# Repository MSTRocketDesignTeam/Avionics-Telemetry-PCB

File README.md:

View this project on [CADLAB.io](https://cadlab.io/project/24983). 

# Overview

This repository contains the PCB files for the main Rocket Telemetry project.

## Purpose and Motivation
This project aims to create flight-rated PCBs that can collect information about the team's rockets as they are launched.

The primary impetus for this project is to develop a student-designed solution to keep the team from losing rockets. This means that these boards must contain and interface with the electronics required to track and analyze a rocket mid-flight and indicate the rocket landing site location to the team back at the launch site to aid in recovery efforts.

The second purpose of this board is to collect and stream performance data about the rocket during all stages of its flight. This data will come from onboard sensors that measure the rocket’s acceleration, altitude, speed, orientation, etc. This will initially only be stored onboard the rocket, with the long-term goal of feeding a real-time 3D model simulation of the rocket’s flight to the team at the launch site. It should also be a goal to include future capabilities for interfacing with external sensors, such as thermocouples, pressure transducers, cameras, and more.

## Inspirations

Initial developments of this board are to be a direct replacement for a Telemetrum V3, with features and design optimizations to be implemented in future revisions.

A [Telemetrum V3](https://altusmetrum.org/TeleMetrum/) is an amateur rocketry telemetry solution from [Altus Metrum](https://altusmetrum.org/index.html).

[Signal](https://bps.space/signal/) from [BPS.Space](https://bps.space/) is a flight computer first and a data collection solution second. It is designed to stream data to the ground station, although it is likely insufficient for the large 10-30k ft class rockets that our team constructs.

An excellent KiCAD tutorial around making a small thumb-drive-sized PCB with an STM32, RF, and USB components: [here on YouTube by Phil's Lab](https://www.youtube.com/watch?v=14_jh3nLSsU) and is an excellent tutorial on using circuit design software and the process/approach you go through making something like this. Highly recommended to watch and maybe take some notes on. This is a solid start for our telemetry board.

# Features

#### Physical

* Expected Size: 53 x 69 mm (Arduino Uno)
* Best Size: Around 75 x 25 mm if possible
* Thin/Long is better than Square
* Rectangular shape w/ rounded edges
* Screw Mounting Holes

#### Primary Components

* STM32 Family Microcontroller
* 900MHz Radio Module
* GPS Receiver
* External RF Antenna Connector

#### Sensors

* Accelerometer
* Magnetometer
* Barometer
* Gyroscope
* Temperature

#### Data

* Flash Storage Chip for inflight capture
* Micro SD Card Reader for postflight storage
* Debugging/programming header

#### Power

* Connection to LiPo Packs
* Coin Cell/Capacitor Battery Backup
* No charge controller
* Low-power mode preflight

# Companion Documentation

[Telemetry Board R&D Documentation Folder - Google Drive](https://drive.google.com/drive/folders/1-Ft9_IYGoKeQ8SOpWUMPCNhws5y90gv3?usp=sharing)

[Component Comparison - Google Sheet](https://docs.google.com/spreadsheets/d/1QPZUW1DP2L5ciMKxbgeHV3uC0-h4SxSqm0nYhaIsA54/edit?usp=sharing)

[Telemetrum V3 Features and Components - Google Doc](https://docs.google.com/document/d/1UKlisEx7MZwDFethEzJ8d39NXyabVl6lI_5ZflczvP4/edit?usp=sharing)

[Telemetry Board Requirement Brainstorm - Google Doc](https://docs.google.com/document/d/1sqFQGxX3MVceV2B7MoNJb_ZmXdHjXhyEQbpknLjsYw0/edit?usp=sharing)

[Telemetry Notepad - Google Doc](https://docs.google.com/document/d/1K5M_XsDRmasx09W511Fg23m5dxfRa6N_FNR6dFqZZKQ/edit?usp=sharing)

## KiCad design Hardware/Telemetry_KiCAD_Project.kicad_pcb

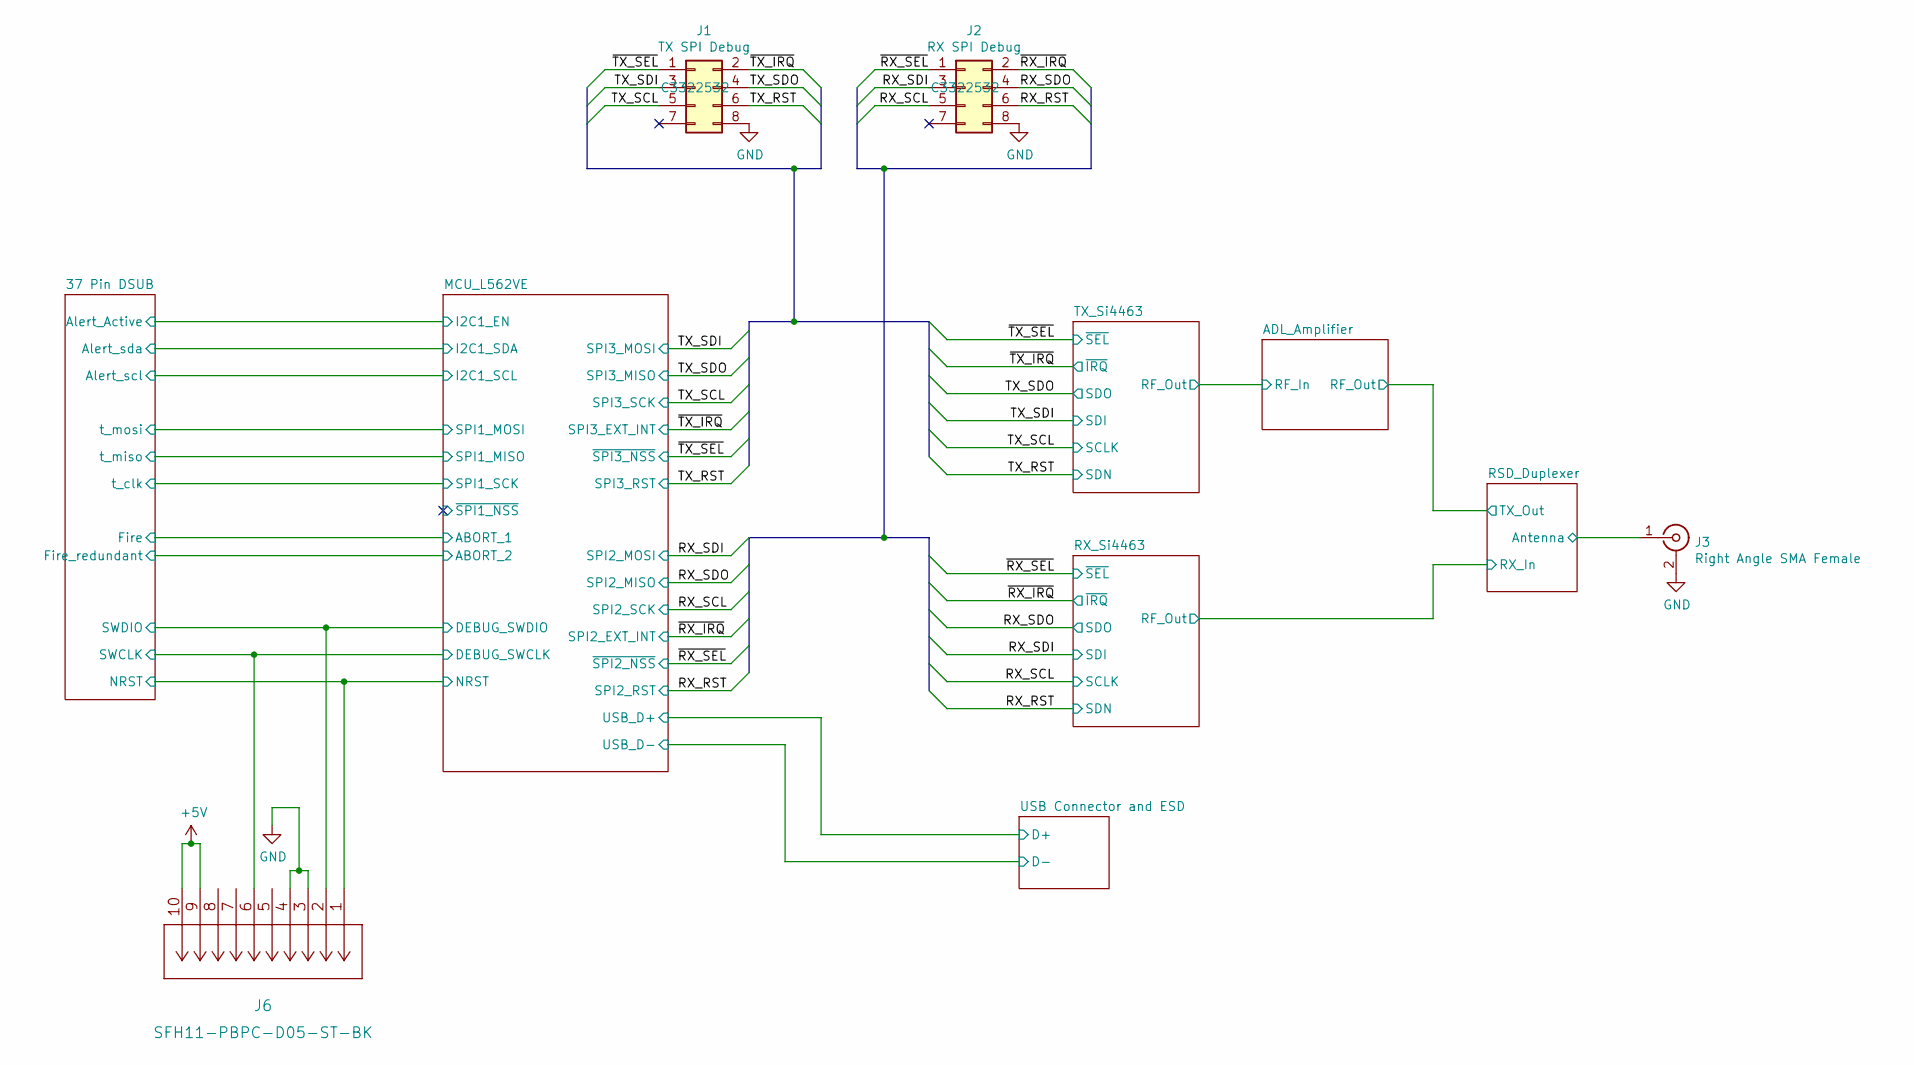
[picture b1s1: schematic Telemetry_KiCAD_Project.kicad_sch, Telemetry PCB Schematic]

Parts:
J1: TX SPI Debug; PinHeader_2x04_P2.54mm_Vertical; LCSC C3322532
J2: RX SPI Debug; PinHeader_2x04_P2.54mm_Vertical; LCSC C3322532
J3: Right Angle SMA Female; SMA_Molex_73251-2200_Horizontal; LCSC C3174425
J6: SFH11-PBPC-D05-ST-BK

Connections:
+5V: J6.9, J6.10; also elsewhere on the board
/37 Pin DSUB/SWCLK: J6.6; also elsewhere on the board
/37 Pin DSUB/SWDIO: J6.2; also elsewhere on the board
/MCU_L562VE/~RESET: J6.1; also elsewhere on the board
/RSD_Duplexer/Antenna: J3.1 (In); also elsewhere on the board
/RX_RST: J2.6; also elsewhere on the board
/RX_SCL: J2.5; also elsewhere on the board
/RX_SDI: J2.3; also elsewhere on the board
/RX_SDO: J2.4; also elsewhere on the board
/TX_RST: J1.6; also elsewhere on the board
/TX_SCL: J1.5; also elsewhere on the board
/TX_SDI: J1.3; also elsewhere on the board
/TX_SDO: J1.4; also elsewhere on the board
/~RX_IRQ: J2.2; also elsewhere on the board
/~RX_SEL: J2.1; also elsewhere on the board
/~TX_IRQ: J1.2; also elsewhere on the board
/~TX_SEL: J1.1; also elsewhere on the board
GND: J1.8, J2.8, J3.2 (Ext), J6.3, J6.4; also elsewhere on the board

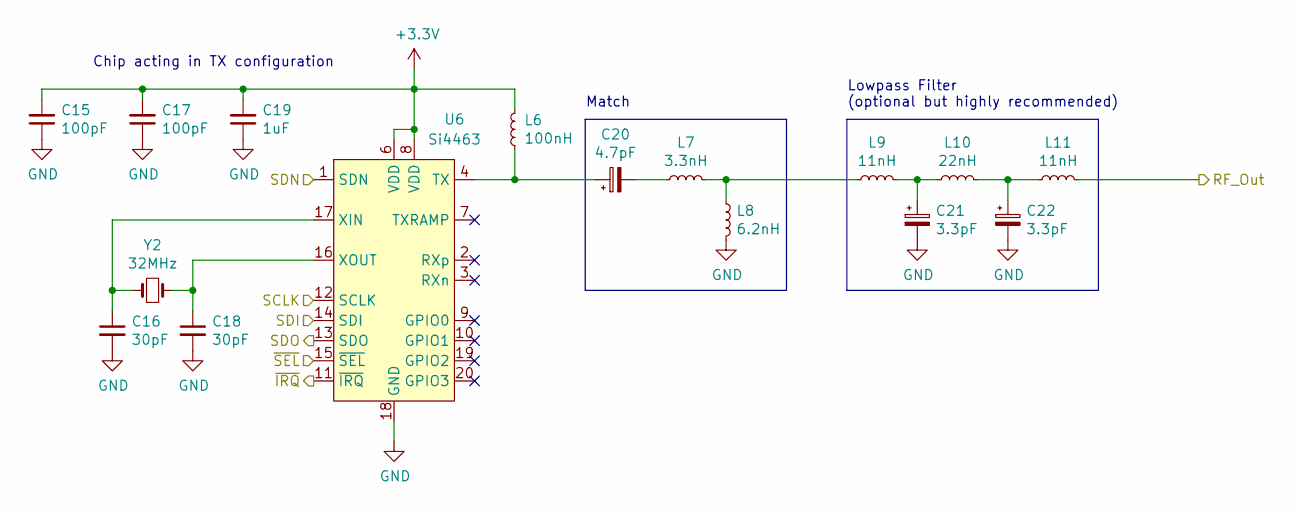
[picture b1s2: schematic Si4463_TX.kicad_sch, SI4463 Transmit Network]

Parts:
C15, C17: 100pF; C_0402_1005Metric; LCSC C1546
C16, C18: 30pF; C_0603_1608Metric_Pad1.08x0.95mm_HandSolder; LCSC C123555
C19: 1uF; C_0402_1005Metric; LCSC C52923
C20: 4.7pF; C_0402_1005Metric; LCSC C1569
C21, C22: 3.3pF; C_0402_1005Metric; LCSC C1565
L6: 100nH; L_0402_1005Metric; LCSC C22726
L7: 3.3nH; L_0402_1005Metric; LCSC C86064
L8: 6.2nH; L_0402_1005Metric; LCSC C87534
L9, L11: 11nH; L_0402_1005Metric; LCSC C27147
L10: 22nH; L_0402_1005Metric; LCSC C15178
U6: Si4463; QFN-20-1EP_4x4mm_P0.5mm_EP2.6x2.6mm_ThermalVias; LCSC C476202
Y2: 32MHz; XTAL_ABM7-32.000MHZ-D2Y-T; LCSC C1986810

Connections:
+3V3: C15.2, C17.2, C19.2, L6.2, U6.6 (VDD), U6.8 (VDD); also elsewhere on the board
/ADL_Amplifier/RF_In: L11.2; also elsewhere on the board
/TX_RST: U6.1 (SDN); also elsewhere on the board
/TX_SCL: U6.12 (SCLK); also elsewhere on the board
/TX_SDI: U6.14 (SDI); also elsewhere on the board
/TX_SDO: U6.13 (SDO); also elsewhere on the board
/~TX_IRQ: U6.11 (~IRQ); also elsewhere on the board
/~TX_SEL: U6.15 (~SEL); also elsewhere on the board
GND: C15.1, C16.2, C17.1, C18.2, C19.1, C21.2, C22.2, L8.2, U6.18 (GND), U6.21 (GND); also elsewhere on the board
unnamed: C16.1, U6.17 (XIN), Y2.1
unnamed: C18.1, U6.16 (XOUT), Y2.2
unnamed: C20.1, L6.1, U6.4 (TX)
unnamed: C20.2, L7.1
unnamed: C21.1, L9.2, L10.1
unnamed: C22.1, L10.2, L11.1
unnamed: L7.2, L8.1, L9.1

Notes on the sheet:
Match
Chip acting in TX configuration
Lowpass Filter (optional but highly recommended)

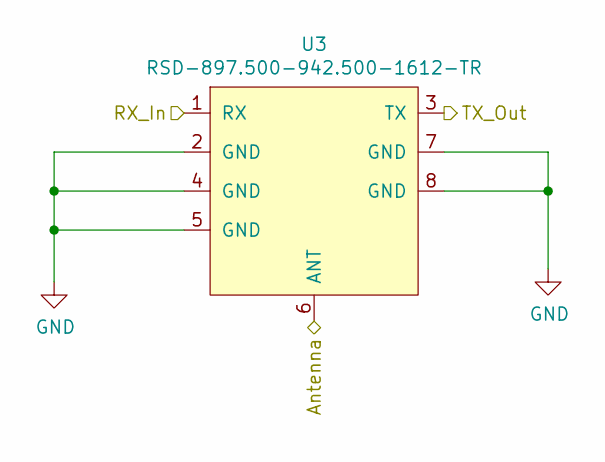
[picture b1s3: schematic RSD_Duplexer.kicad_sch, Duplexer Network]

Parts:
U3: RSD-897.500-942.500-1612-TR; LCSC C3271762

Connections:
/ADL_Amplifier/RF_Out: U3.3 (TX); also elsewhere on the board
/RSD_Duplexer/Antenna: U3.6 (ANT); also elsewhere on the board
/RSD_Duplexer/RX_In: U3.1 (RX); also elsewhere on the board
GND: U3.2 (GND), U3.4 (GND), U3.5 (GND), U3.7 (GND), U3.8 (GND); also elsewhere on the board

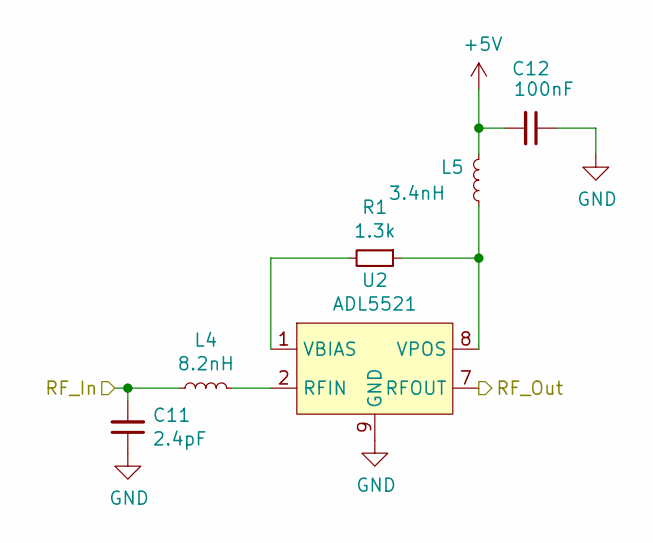
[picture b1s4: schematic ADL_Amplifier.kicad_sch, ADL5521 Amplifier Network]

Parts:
C11: 2.4pF; C_0402_1005Metric; LCSC C123475
C12: 100nF; C_0402_1005Metric; LCSC C307331
L4: 8.2nH; L_0402_1005Metric; LCSC C16208
L5: 3.4nH; L_0402_1005Metric; LCSC C86064
R1: 1.3k; R_0402_1005Metric; LCSC C25866
U2: ADL5521; LFCSP-8-1EP_3x3mm_P0.5mm_EP1.45x1.74mm; LCSC C657768

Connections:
+5V: C12.2, L5.2; also elsewhere on the board
/ADL_Amplifier/RF_In: C11.2, L4.1; also elsewhere on the board
/ADL_Amplifier/RF_Out: U2.7 (RFOUT); also elsewhere on the board
GND: C11.1, C12.1, U2.9 (GND); also elsewhere on the board
unnamed: L4.2, U2.2 (RFIN)
unnamed: L5.1, R1.1, U2.8 (VPOS)
unnamed: R1.2, U2.1 (VBIAS)

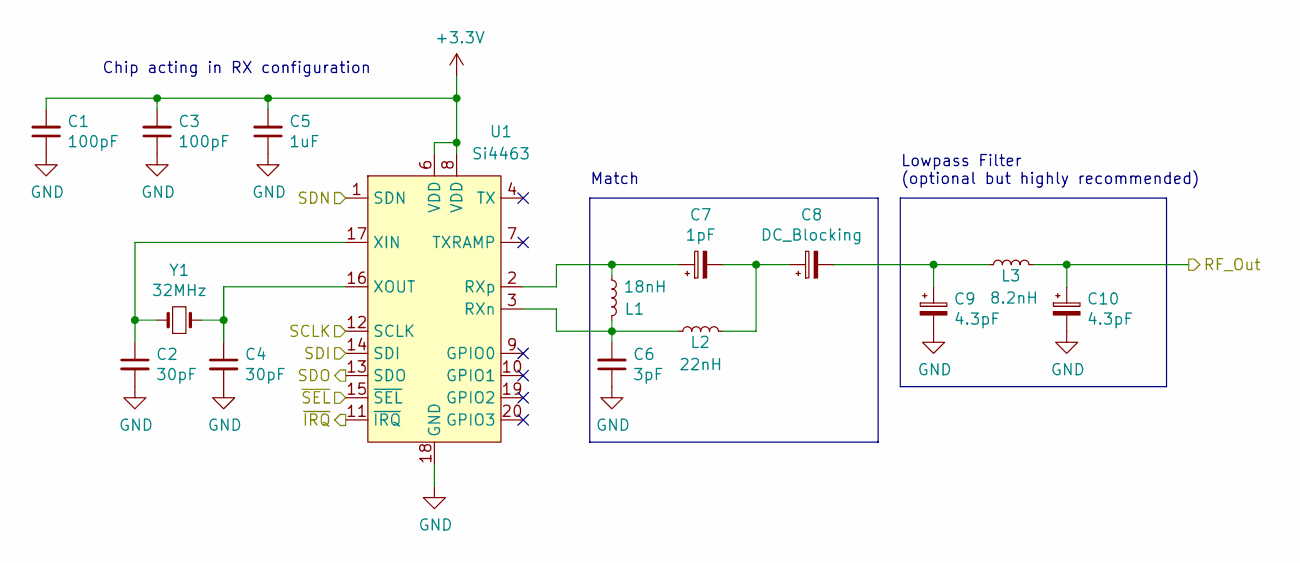
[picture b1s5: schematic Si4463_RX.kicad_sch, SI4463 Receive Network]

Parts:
C1, C3: 100pF; C_0402_1005Metric; LCSC C1546
C2, C4: 30pF; C_0603_1608Metric_Pad1.08x0.95mm_HandSolder; LCSC C123555
C5: 1uF; C_0402_1005Metric; LCSC C52923
C6: 3pF; C_0402_1005Metric; LCSC C115630
C7: 1pF; C_0402_1005Metric; LCSC C1550
C8: DC_Blocking; C_0402_1005Metric; LCSC C1550
C9, C10: 4.3pF; C_0402_1005Metric; LCSC C159803
L1: 18nH; L_0402_1005Metric; LCSC C24562
L2: 22nH; L_0402_1005Metric; LCSC C15178
L3: 8.2nH; L_0402_1005Metric; LCSC C16208
U1: Si4463; QFN-20-1EP_4x4mm_P0.5mm_EP2.6x2.6mm_ThermalVias; LCSC C476202
Y1: 32MHz; XTAL_ABM7-32.000MHZ-D2Y-T; LCSC C1986810

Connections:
+3V3: C1.2, C3.2, C5.2, U1.6 (VDD), U1.8 (VDD); also elsewhere on the board
/RSD_Duplexer/RX_In: C10.1, L3.2; also elsewhere on the board
/RX_RST: U1.1 (SDN); also elsewhere on the board
/RX_SCL: U1.12 (SCLK); also elsewhere on the board
/RX_SDI: U1.14 (SDI); also elsewhere on the board
/RX_SDO: U1.13 (SDO); also elsewhere on the board
/~RX_IRQ: U1.11 (~IRQ); also elsewhere on the board
/~RX_SEL: U1.15 (~SEL); also elsewhere on the board
GND: C1.1, C2.2, C3.1, C4.2, C5.1, C6.1, C9.2, C10.2, U1.18 (GND), U1.21 (GND); also elsewhere on the board
unnamed: C2.1, U1.17 (XIN), Y1.1
unnamed: C4.1, U1.16 (XOUT), Y1.2
unnamed: C6.2, L1.2, L2.1, U1.3 (RXn)
unnamed: C7.1, L1.1, U1.2 (RXp)
unnamed: C7.2, C8.1, L2.2
unnamed: C8.2, C9.1, L3.1

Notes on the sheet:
Chip acting in RX configuration
Lowpass Filter (optional but highly recommended)
Match

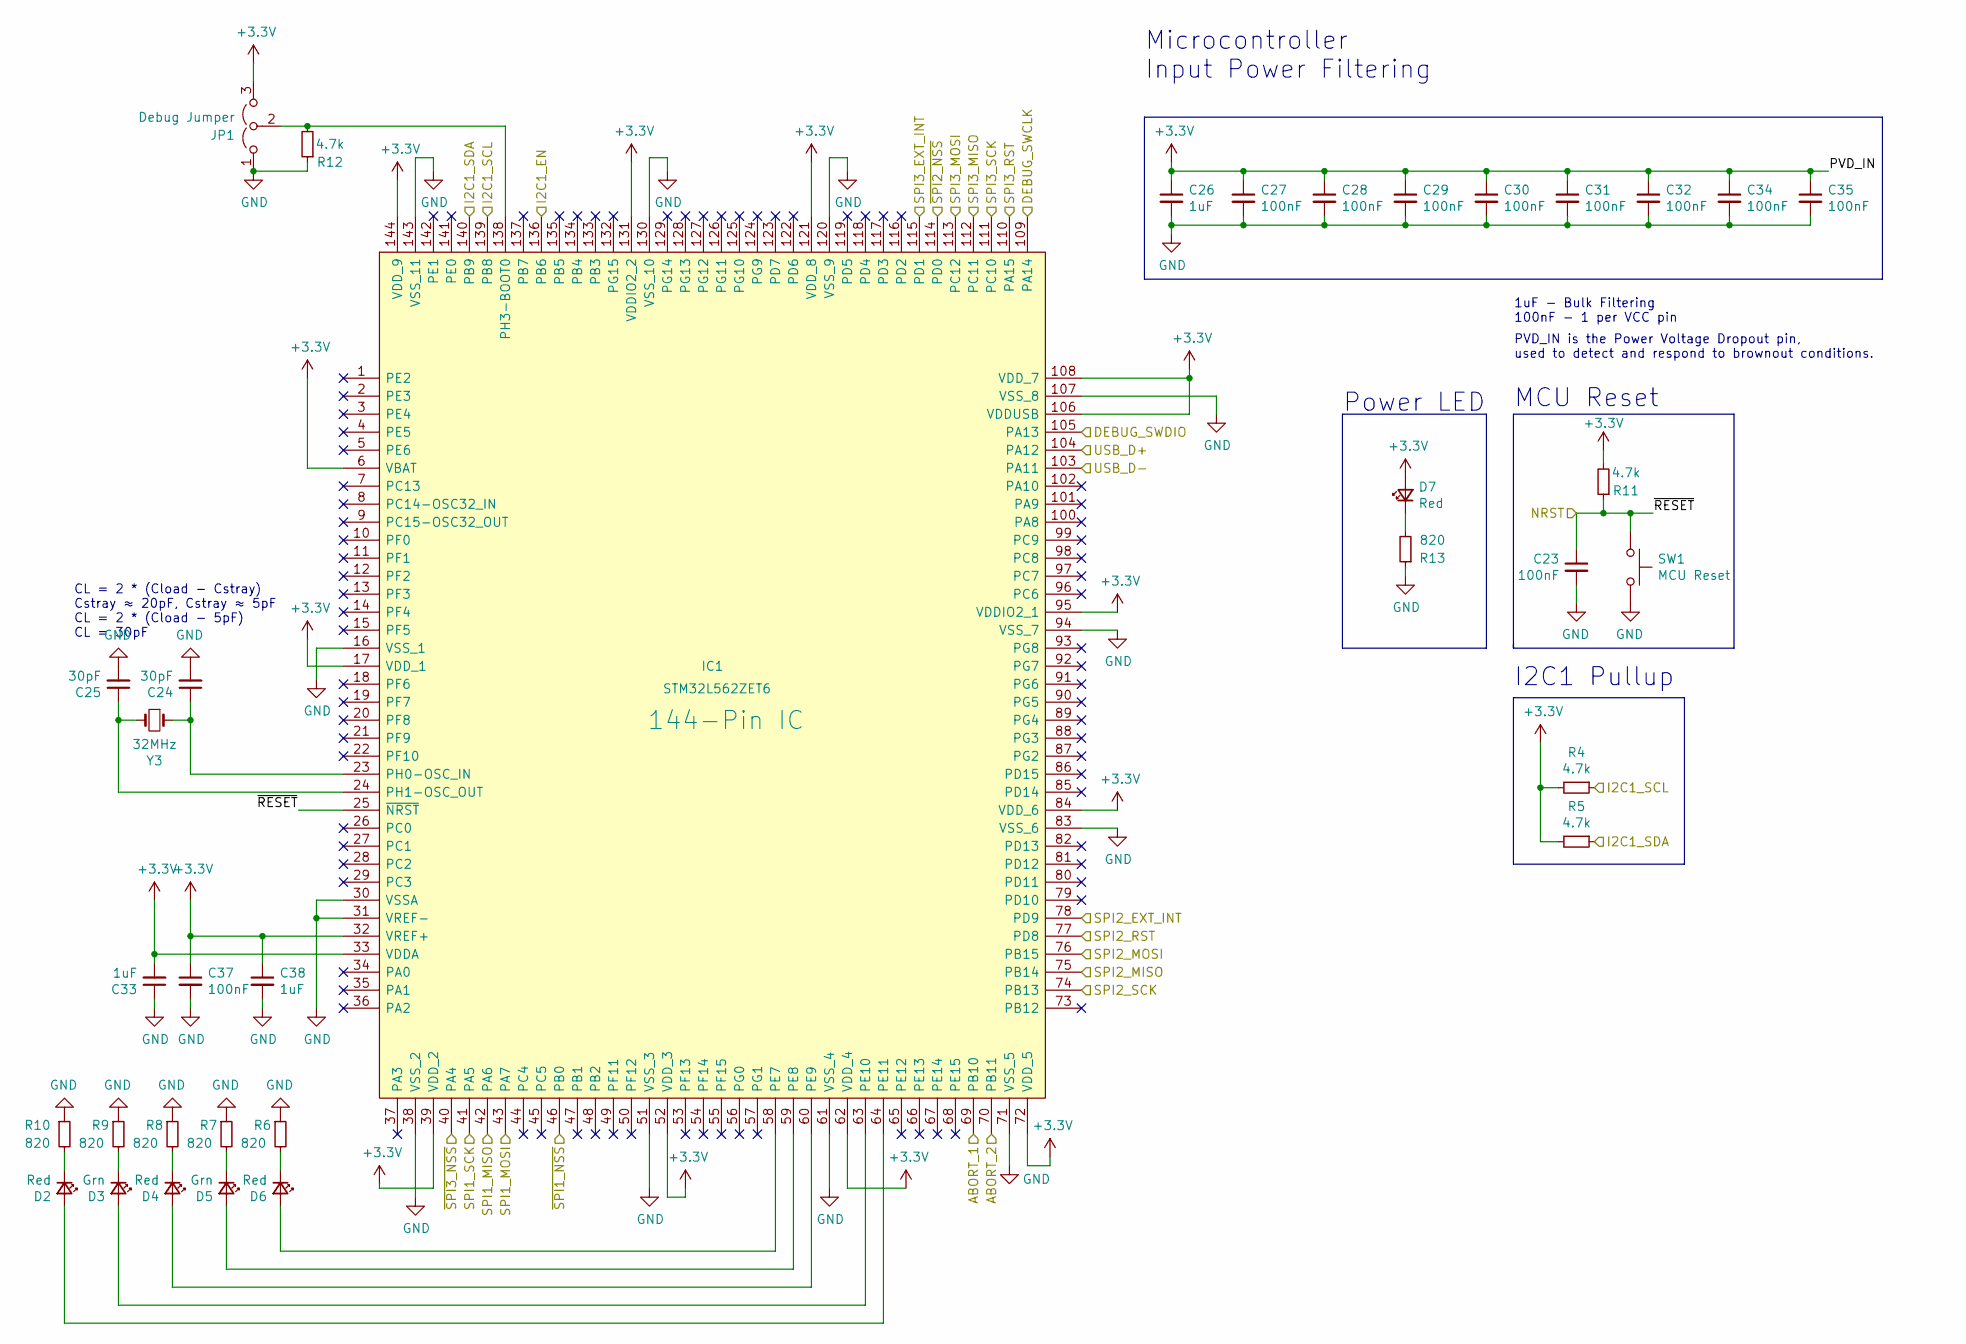
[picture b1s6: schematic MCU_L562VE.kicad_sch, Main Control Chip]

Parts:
C23, C27, C28, C29, C30, C31, C32, C34, C35, C37: 100nF; C_0603_1608Metric_Pad1.08x0.95mm_HandSolder; LCSC C14663
C24, C25: 30pF; C_0603_1608Metric_Pad1.08x0.95mm_HandSolder; LCSC C123555
C26: 1uF; C_0603_1608Metric_Pad1.08x0.95mm_HandSolder; LCSC C15849
C33, C38: 1uF; C_0603_1608Metric_Pad1.08x0.95mm_HandSolder; LCSC C14663
D2, D4, D6, D7: Red; LED_0603_1608Metric_Pad1.05x0.95mm_HandSolder; LCSC C2286
D3, D5: Grn; LED_0603_1608Metric_Pad1.05x0.95mm_HandSolder; LCSC C434423
IC1: STM32L562ZET6; QFP50P2200X2200X160-144N; Mouser Part Number 511-STM32L562ZET6
JP1: Debug Jumper; PinHeader_1x03_P2.54mm_Vertical; LCSC C5346215
R4, R5: 4.7k; R_0603_1608Metric_Pad1.05x0.95mm_HandSolder; LCSC C25999
R6, R7, R8, R9, R10: 820; R_0603_1608Metric_Pad1.05x0.95mm_HandSolder; LCSC C23253
R11, R12: 4.7k; R_0603_1608Metric_Pad0.98x0.95mm_HandSolder; LCSC C25999
R13: 820; R_0603_1608Metric; LCSC C23253
SW1: MCU Reset; SW_SPST_PTS645; LCSC C2837531
Y3: 32MHz; XTAL_ABM7-32.000MHZ-D2Y-T; LCSC C1986810

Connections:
+3V3: C26.1, C27.1, C28.1, C29.1, C30.1, C31.1, C32.1, C33.2, C34.1, C35.1, C37.1, C38.1, D7.2 (A), IC1.6 (VBAT), IC1.17 (VDD_1), IC1.32 (VREF+), IC1.33 (VDDA), IC1.39 (VDD_2), IC1.52 (VDD_3), IC1.62 (VDD_4), IC1.72 (VDD_5), IC1.84 (VDD_6), IC1.95 (VDDIO2_1), IC1.106 (VDDUSB), IC1.108 (VDD_7), IC1.121 (VDD_8), IC1.131 (VDDIO2_2), IC1.144 (VDD_9), JP1.3 (B), R4.2, R5.2, R11.2; also elsewhere on the board
/37 Pin DSUB/Alert_Active: IC1.136 (PB6); also elsewhere on the board
/37 Pin DSUB/Alert_scl: IC1.139 (PB8), R4.1; also elsewhere on the board
/37 Pin DSUB/Alert_sda: IC1.140 (PB9), R5.1; also elsewhere on the board
/37 Pin DSUB/Fire: IC1.69 (PB10); also elsewhere on the board
/37 Pin DSUB/Fire_redundant: IC1.70 (PB11); also elsewhere on the board
/37 Pin DSUB/SWCLK: IC1.109 (PA14); also elsewhere on the board
/37 Pin DSUB/SWDIO: IC1.105 (PA13); also elsewhere on the board
/37 Pin DSUB/t_clk: IC1.41 (PA5); also elsewhere on the board
/37 Pin DSUB/t_miso: IC1.42 (PA6); also elsewhere on the board
/37 Pin DSUB/t_mosi: IC1.43 (PA7); also elsewhere on the board
/MCU_L562VE/USB_D+: IC1.104 (PA12); also elsewhere on the board
/MCU_L562VE/USB_D-: IC1.103 (PA11); also elsewhere on the board
/MCU_L562VE/~RESET: C23.1, IC1.25 (~NRST), R11.1, SW1.1; also elsewhere on the board
/MCU_L562VE/~SPI1_NSS: IC1.46 (PB0)
/RX_RST: IC1.77 (PD8); also elsewhere on the board
/RX_SCL: IC1.74 (PB13); also elsewhere on the board
/RX_SDI: IC1.76 (PB15); also elsewhere on the board
/RX_SDO: IC1.75 (PB14); also elsewhere on the board
/TX_RST: IC1.110 (PA15); also elsewhere on the board
/TX_SCL: IC1.111 (PC10); also elsewhere on the board
/TX_SDI: IC1.113 (PC12); also elsewhere on the board
/TX_SDO: IC1.112 (PC11); also elsewhere on the board
/~RX_IRQ: IC1.78 (PD9); also elsewhere on the board
/~RX_SEL: IC1.114 (PD0); also elsewhere on the board
/~TX_IRQ: IC1.115 (PD1); also elsewhere on the board
/~TX_SEL: IC1.40 (PA4); also elsewhere on the board
GND: C23.2, C24.2, C25.2, C26.2, C27.2, C28.2, C29.2, C30.2, C31.2, C32.2, C33.1, C34.2, C35.2, C37.2, C38.2, IC1.16 (VSS_1), IC1.30 (VSSA), IC1.31 (VREF-), IC1.38 (VSS_2), IC1.51 (VSS_3), IC1.61 (VSS_4), IC1.71 (VSS_5), IC1.83 (VSS_6), IC1.94 (VSS_7), IC1.107 (VSS_8), IC1.120 (VSS_9), IC1.130 (VSS_10), IC1.143 (VSS_11), JP1.1 (A), R6.1, R7.1, R8.1, R9.1, R10.1, R12.1, R13.1, SW1.2; also elsewhere on the board
unnamed: C24.1, IC1.23 (PH0-OSC_IN), Y3.1
unnamed: C25.1, IC1.24 (PH1-OSC_OUT), Y3.2
unnamed: D2.1 (K), R10.2
unnamed: D2.2 (A), IC1.64 (PE11)
unnamed: D3.1 (K), R9.2
unnamed: D3.2 (A), IC1.63 (PE10)
unnamed: D4.1 (K), R8.2
unnamed: D4.2 (A), IC1.60 (PE9)
unnamed: D5.1 (K), R7.2
unnamed: D5.2 (A), IC1.59 (PE8)
unnamed: D6.1 (K), R6.2
unnamed: D6.2 (A), IC1.58 (PE7)
unnamed: D7.1 (K), R13.2
unnamed: IC1.138 (PH3-BOOT0), JP1.2 (C), R12.2

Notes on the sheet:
Microcontroller Input Power Filtering
I2C1 Pullup
MCU Reset
PVD_IN is the Power Voltage Dropout pin, used to detect and respond to brownout conditions.
1uF - Bulk Filtering 100nF - 1 per VCC pin
Power LED
CL = 2 * (Cload - Cstray) Cstray ≈ 20pF, Cstray ≈ 5pF CL = 2 * (Cload - 5pF) CL = 30pF

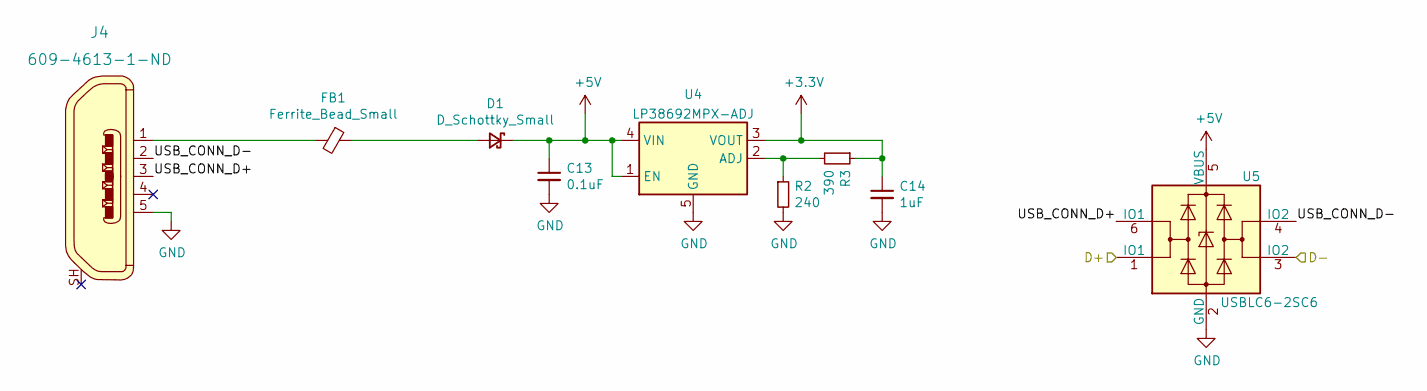
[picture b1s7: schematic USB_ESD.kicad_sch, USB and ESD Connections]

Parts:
C13: 0.1uF; C_0603_1608Metric_Pad1.08x0.95mm_HandSolder; LCSC C14663
C14: 1uF; C_0603_1608Metric_Pad1.08x0.95mm_HandSolder; LCSC C15849
D1: D_Schottky_Small; D_0805_2012Metric_Pad1.15x1.40mm_HandSolder; LCSC C22624
FB1: Ferrite_Bead_Small; C_0603_1608Metric_Pad1.08x0.95mm_HandSolder; LCSC C76892
J4: 609-4613-1-ND; USB_Micro_B_Female_10118192; LCSC C132564
R2: 240; R_0603_1608Metric_Pad0.98x0.95mm_HandSolder; LCSC C23350
R3: 390; R_0603_1608Metric_Pad0.98x0.95mm_HandSolder; LCSC C23151
U4: LP38692MPX-ADJ; SOT-223-5; LCSC C527485
U5: USBLC6-2SC6; SOT-23-6; LCSC C7519

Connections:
+3V3: C14.1, R3.1, U4.3 (VOUT); also elsewhere on the board
+5V: C13.1, D1.1 (K), U4.1 (EN), U4.4 (VIN), U5.5 (VBUS); also elsewhere on the board
/MCU_L562VE/USB_D+: U5.1 (IO1); also elsewhere on the board
/MCU_L562VE/USB_D-: U5.3 (IO2); also elsewhere on the board
/USB Connector and ESD/USB_CONN_D+: J4.3, U5.6 (IO1)
/USB Connector and ESD/USB_CONN_D-: J4.2, U5.4 (IO2)
GND: C13.2, C14.2, J4.5, R2.2, U4.5 (GND), U5.2 (GND); also elsewhere on the board
unnamed: D1.2 (A), FB1.1
unnamed: FB1.2, J4.1
unnamed: R2.1, R3.2, U4.2 (ADJ)

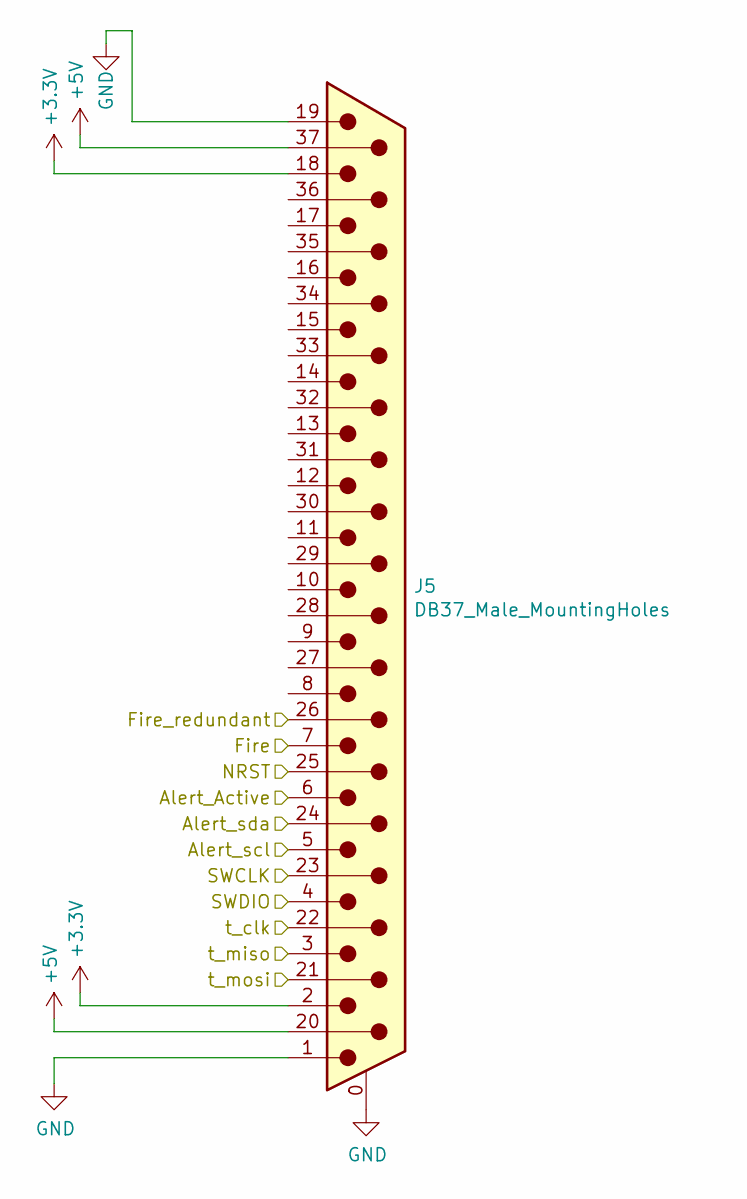
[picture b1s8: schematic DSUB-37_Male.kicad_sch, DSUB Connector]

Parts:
J5: DB37_Male_MountingHoles; L717SDC37P1ACH4F

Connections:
+3V3: J5.2, J5.18; also elsewhere on the board
+5V: J5.20, J5.37; also elsewhere on the board
/37 Pin DSUB/Alert_Active: J5.6; also elsewhere on the board
/37 Pin DSUB/Alert_scl: J5.5; also elsewhere on the board
/37 Pin DSUB/Alert_sda: J5.24; also elsewhere on the board
/37 Pin DSUB/Fire: J5.7; also elsewhere on the board
/37 Pin DSUB/Fire_redundant: J5.26; also elsewhere on the board
/37 Pin DSUB/SWCLK: J5.23; also elsewhere on the board
/37 Pin DSUB/SWDIO: J5.4; also elsewhere on the board
/37 Pin DSUB/t_clk: J5.22; also elsewhere on the board
/37 Pin DSUB/t_miso: J5.3; also elsewhere on the board
/37 Pin DSUB/t_mosi: J5.21; also elsewhere on the board
/MCU_L562VE/~RESET: J5.25; also elsewhere on the board
GND: J5.0 (PAD), J5.1, J5.19; also elsewhere on the board

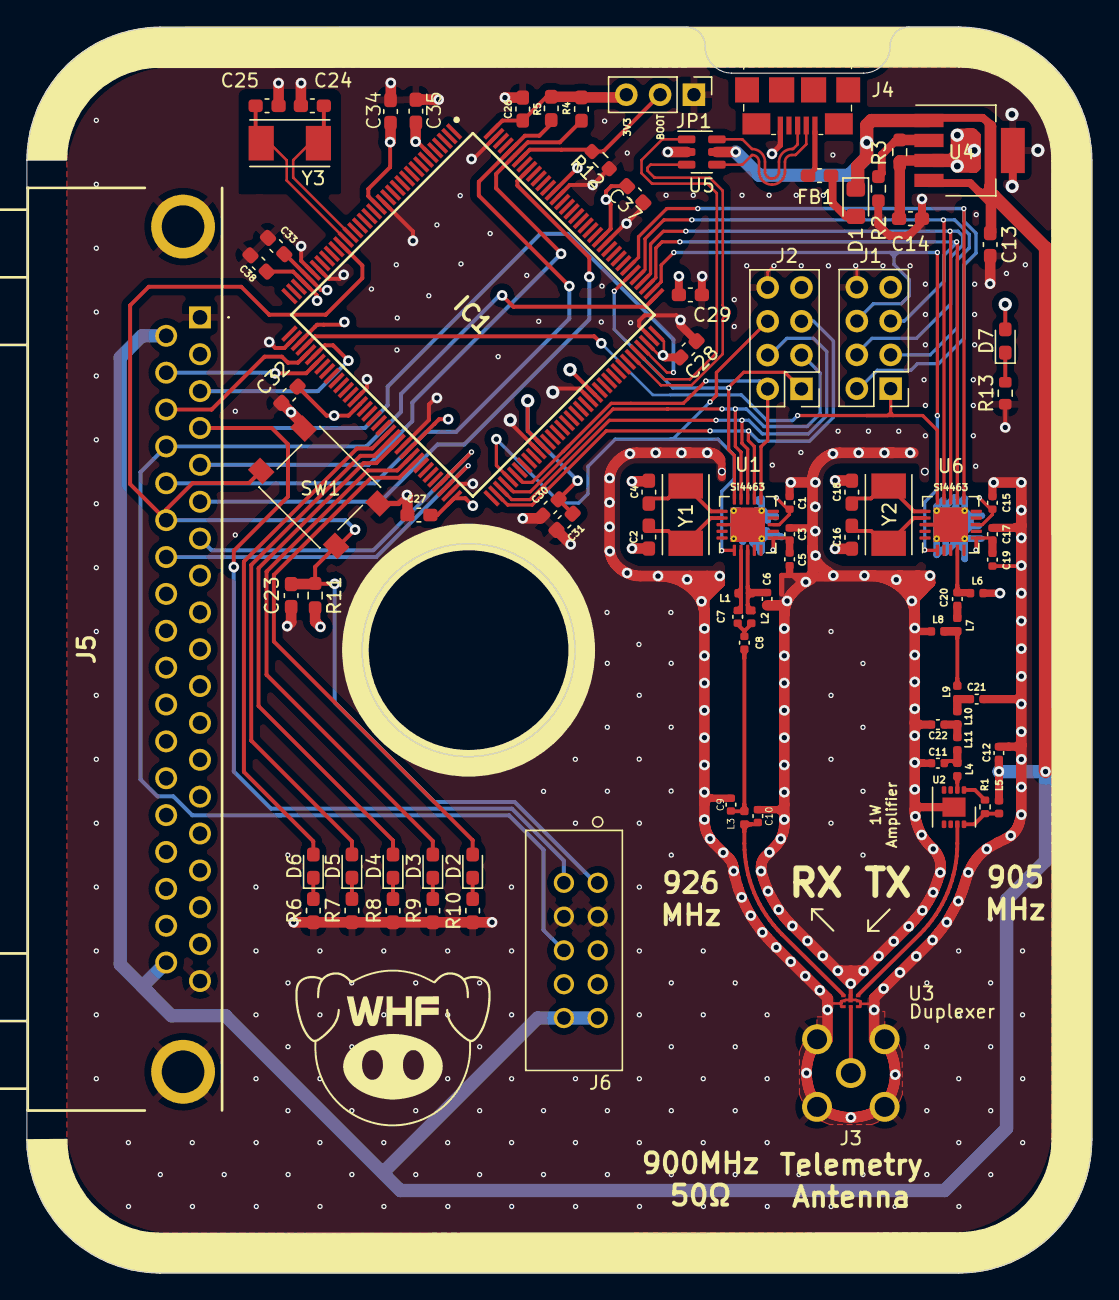
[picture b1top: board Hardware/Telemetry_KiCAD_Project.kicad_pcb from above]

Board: 4 copper layers, 80.0 x 93.6 mm, 87 parts (0 on the bottom side), 67 nets.

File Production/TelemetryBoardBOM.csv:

Comment,Designator,Footprint,LCSC
"2.4pF","C11","Capacitor_SMD:C_0402_1005Metric","C123475"
"100nF","C12","Capacitor_SMD:C_0402_1005Metric","C307331"
"0.1uF","C13","Capacitor_SMD:C_0603_1608Metric_Pad1.08x0.95mm_HandSolder","C14663"
"100pF","C1,C3,C15,C17","Capacitor_SMD:C_0402_1005Metric","C1546 "
"1uF","C5,C19","Capacitor_SMD:C_0402_1005Metric","C52923"
"4.7pF","C20","Capacitor_SMD:C_0402_1005Metric"," C1569 "
"3.3pF","C21,C22","Capacitor_SMD:C_0402_1005Metric","C1565"
"100nF","C23,C27,C28,C29,C30,C31,C32,C34,C35,C37","Capacitor_SMD:C_0603_1608Metric_Pad1.08x0.95mm_HandSolder","C14663"
"30pF","C2,C4,C16,C18,C24,C25","Capacitor_SMD:C_0603_1608Metric_Pad1.08x0.95mm_HandSolder","C123555"
"1uF","C14,C26,C33,C38","Capacitor_SMD:C_0603_1608Metric_Pad1.08x0.95mm_HandSolder","C15849 "
"3pF","C6","Capacitor_SMD:C_0402_1005Metric","C115630"
"1pF","C7","Capacitor_SMD:C_0402_1005Metric"," C1550 "
"DC_Blocking","C8","Capacitor_SMD:C_0402_1005Metric"," C1550 "
"4.3pF","C9,C10","Capacitor_SMD:C_0402_1005Metric","C159803 "
"D_Schottky_Small","D1","Diode_SMD:D_0805_2012Metric_Pad1.15x1.40mm_HandSolder","C22624"
"Red","D2,D4,D6","LED_SMD:LED_0603_1608Metric_Pad1.05x0.95mm_HandSolder"," C2286 "
"Grn","D3,D5","LED_SMD:LED_0603_1608Metric_Pad1.05x0.95mm_HandSolder","C434423"
"Ferrite_Bead_Small","FB1","Capacitor_SMD:C_0603_1608Metric_Pad1.08x0.95mm_HandSolder","C76892 "
"STM32L562ZET6","IC1","QFP50P2200X2200X160-144N","C1236660"
"TX SPI Debug","J1","Connector_PinHeader_2.54mm:PinHeader_2x04_P2.54mm_Vertical","C3322532"
"RX SPI Debug","J2","Connector_PinHeader_2.54mm:PinHeader_2x04_P2.54mm_Vertical","C3322532"
"Right Angle SMA Female","J3","Connector_Coaxial:SMA_Molex_73251-2200_Horizontal","C3174425"
"609-4613-1-ND","J4","digikeyUSBConnector:USB_Micro_B_Female_10118192","C132564"
"DB37_Male_MountingHoles","J5","RDT_Custom_Footprints:L717SDC37P1ACH4F",""
"Debug Jumper","JP1","Connector_PinHeader_2.54mm:PinHeader_1x03_P2.54mm_Vertical","C5346215"
"18nH","L1","Inductor_SMD:L_0402_1005Metric","C24562"
"22nH","L2,L10","Inductor_SMD:L_0402_1005Metric","C15178"
"8.2nH","L3,L4","Inductor_SMD:L_0402_1005Metric","C16208"
"3.4nH","L5","Inductor_SMD:L_0402_1005Metric","C86064"
"100nH","L6","Inductor_SMD:L_0402_1005Metric","C22726"
"3.3nH","L7","Inductor_SMD:L_0402_1005Metric","C86064"
"6.2nH","L8","Inductor_SMD:L_0402_1005Metric","C87534 "
"11nH","L9,L11","Inductor_SMD:L_0402_1005Metric","C27147"
"1.3k","R1","Resistor_SMD:R_0402_1005Metric","C25866 "
"4.7k","R11,R12","Resistor_SMD:R_0603_1608Metric_Pad0.98x0.95mm_HandSolder","C25999"
"240","R2","Resistor_SMD:R_0603_1608Metric_Pad0.98x0.95mm_HandSolder","C23350"
"390","R3","Resistor_SMD:R_0603_1608Metric_Pad0.98x0.95mm_HandSolder","C23151"
"4.7k","R4,R5","Resistor_SMD:R_0603_1608Metric_Pad1.05x0.95mm_HandSolder","C25999"
"820","R6,R7,R8,R9,R10","Resistor_SMD:R_0603_1608Metric_Pad1.05x0.95mm_HandSolder"," C23253"
"MCU Reset","SW1","Button_Switch_SMD:SW_SPST_PTS645","C2837531 "
"ADL5521","U2","Package_CSP:LFCSP-8-1EP_3x3mm_P0.5mm_EP1.45x1.74mm","C657768"
"RSD-897.500-942.500-1612-TR","U3","RDT_Custom_Footprints:RSD-897.500-942.500-1612-TR","C3271762"
"LP38692MPX-ADJ","U4","Package_TO_SOT_SMD:SOT-223-5","C527485"
"USBLC6-2SC6","U5","Package_TO_SOT_SMD:SOT-23-6","C7519"
"Si4463","U1,U6","Package_DFN_QFN:QFN-20-1EP_4x4mm_P0.5mm_EP2.6x2.6mm_ThermalVias","C476202"
"32MHz","Y1,Y2,Y3","RDT_Custom_Footprints:XTAL_ABM7-32.000MHZ-D2Y-T","C1986810"

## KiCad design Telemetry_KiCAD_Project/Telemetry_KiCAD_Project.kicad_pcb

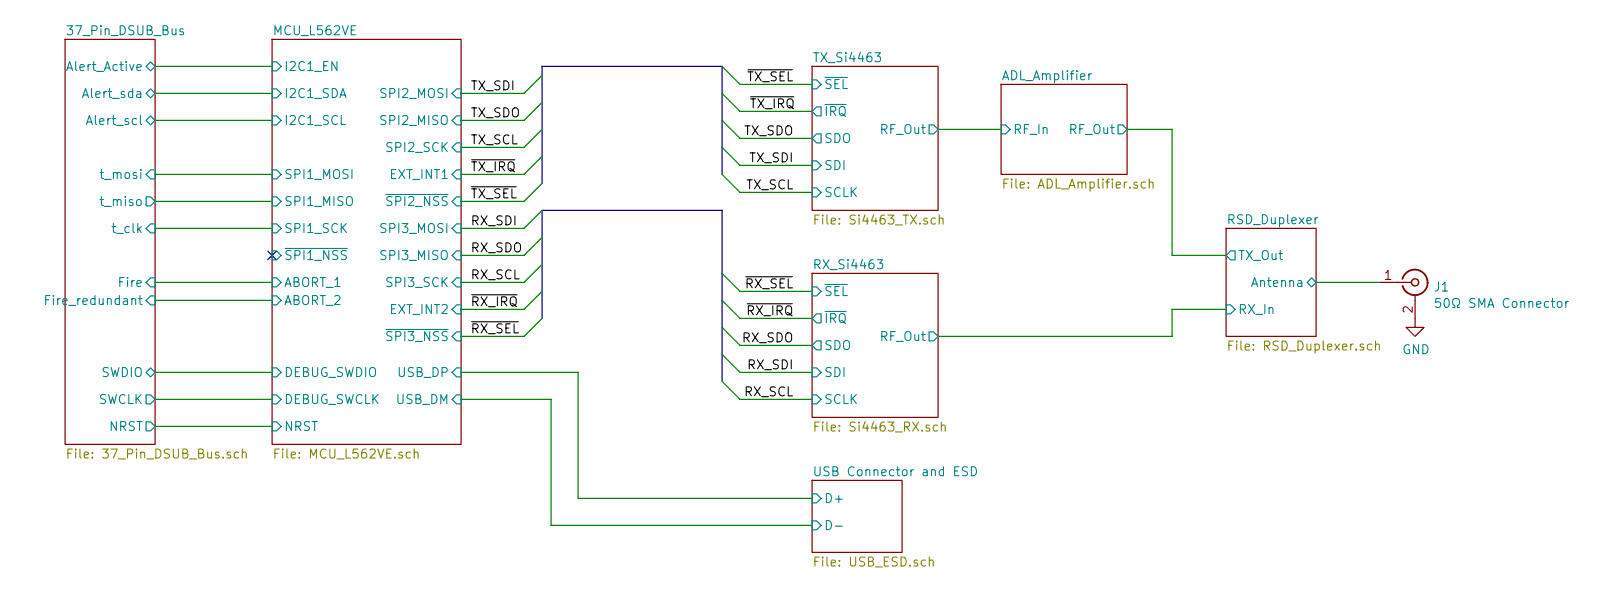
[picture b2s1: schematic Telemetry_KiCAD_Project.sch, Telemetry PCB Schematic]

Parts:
J1: 50Ω SMA Connector; SMA_Amphenol_132134-11_Vertical

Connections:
/RSD_Duplexer/Antenna: J1.1 (In); also elsewhere on the board
GND: J1.2 (Ext); also elsewhere on the board

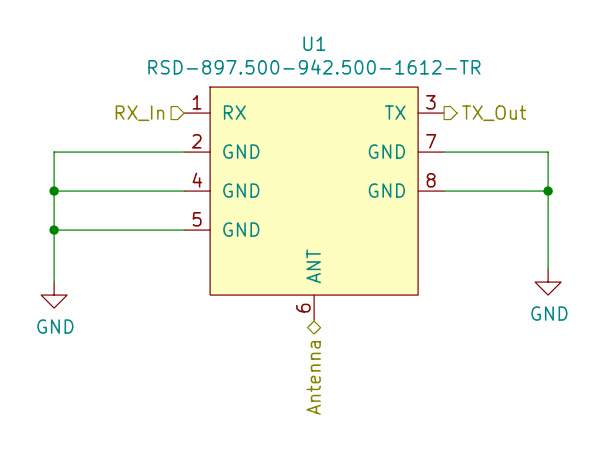
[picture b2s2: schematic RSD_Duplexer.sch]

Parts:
U1: RSD-897.500-942.500-1612-TR

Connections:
/ADL_Amplifier/RF_Out: U1.3 (TX); also elsewhere on the board
/RSD_Duplexer/Antenna: U1.6 (ANT); also elsewhere on the board
/RX_Si4463/RF_Out: U1.1 (RX); also elsewhere on the board
GND: U1.2 (GND), U1.4 (GND), U1.5 (GND), U1.7 (GND), U1.8 (GND); also elsewhere on the board

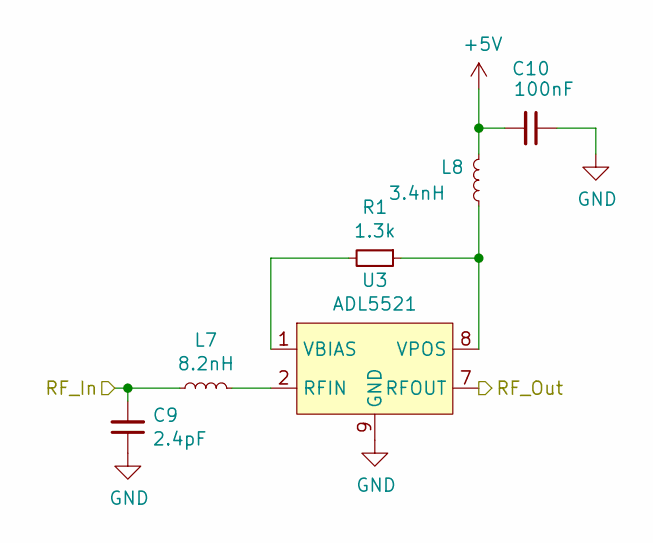
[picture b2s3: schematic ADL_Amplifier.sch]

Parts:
C9: 2.4pF; C_0603_1608Metric
C10: 100nF; C_0603_1608Metric
L7: 8.2nH; L_0603_1608Metric
L8: 3.4nH; L_0603_1608Metric
R1: 1.3k; 0603
U3: ADL5521; LFCSP-8-1EP_3x3mm_P0.5mm_EP1.45x1.74mm

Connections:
+5V: C10.2, L8.2; also elsewhere on the board
/ADL_Amplifier/RF_In: C9.2, L7.1; also elsewhere on the board
/ADL_Amplifier/RF_Out: U3.7 (RFOUT); also elsewhere on the board
GND: C9.1, C10.1, U3.9 (GND); also elsewhere on the board
unnamed: L7.2, U3.2 (RFIN)
unnamed: L8.1, R1.1, U3.8 (VPOS)
unnamed: R1.2, U3.1 (VBIAS)

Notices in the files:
parts and their libraries:
Copyright 2021 Accelerated Designs. All rights reserved.
